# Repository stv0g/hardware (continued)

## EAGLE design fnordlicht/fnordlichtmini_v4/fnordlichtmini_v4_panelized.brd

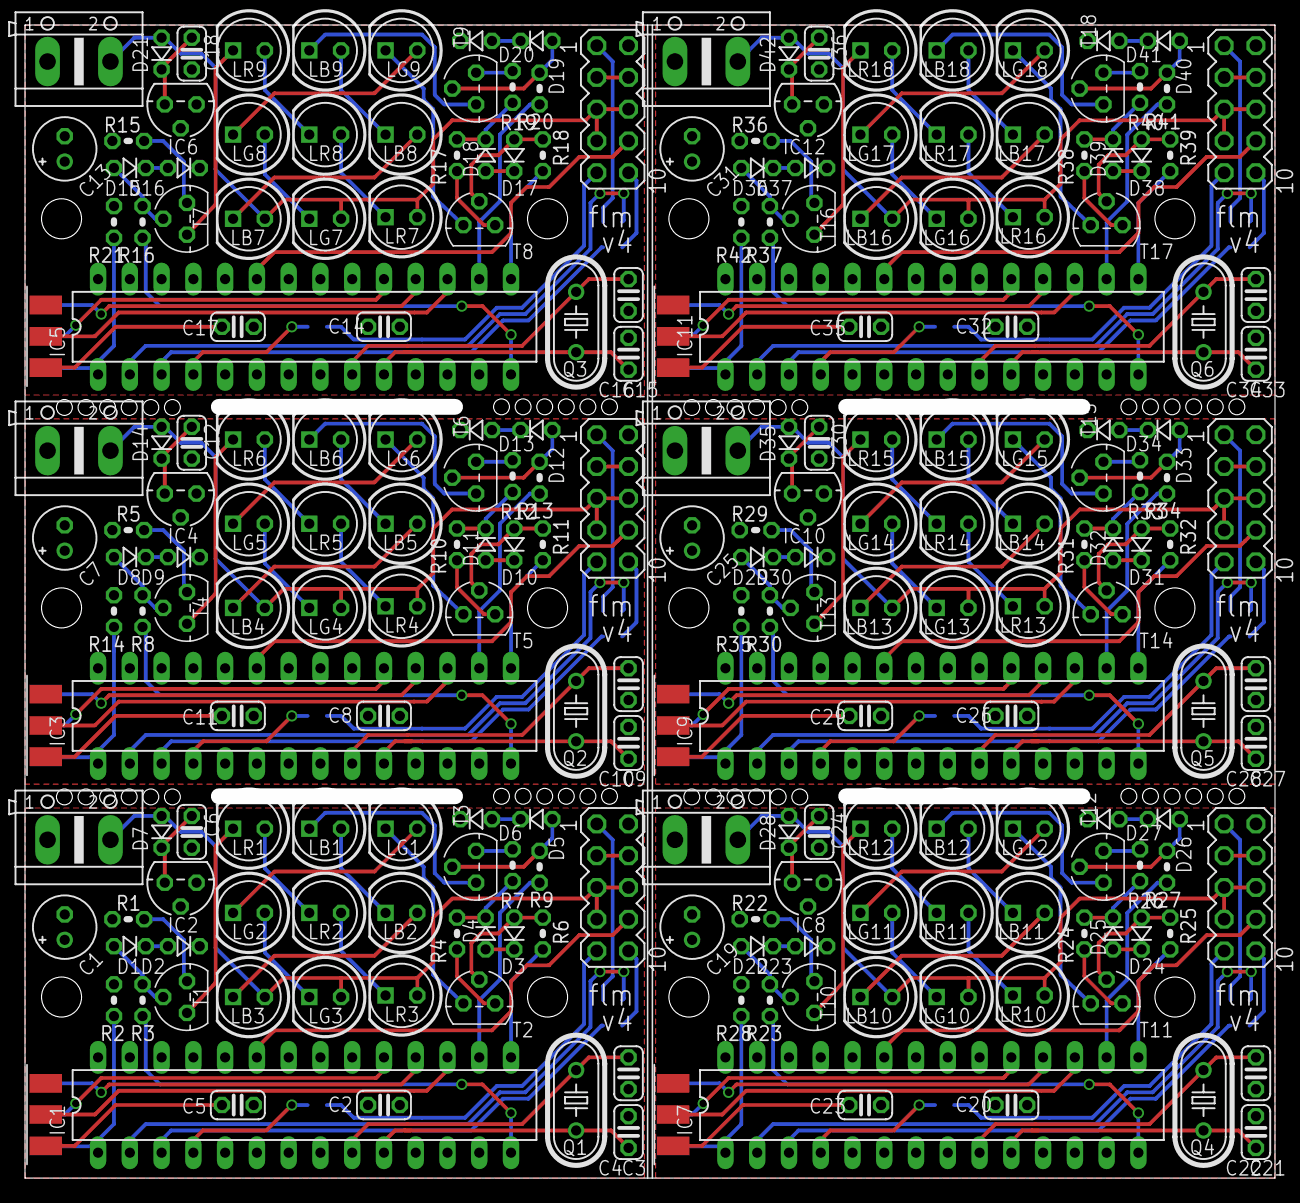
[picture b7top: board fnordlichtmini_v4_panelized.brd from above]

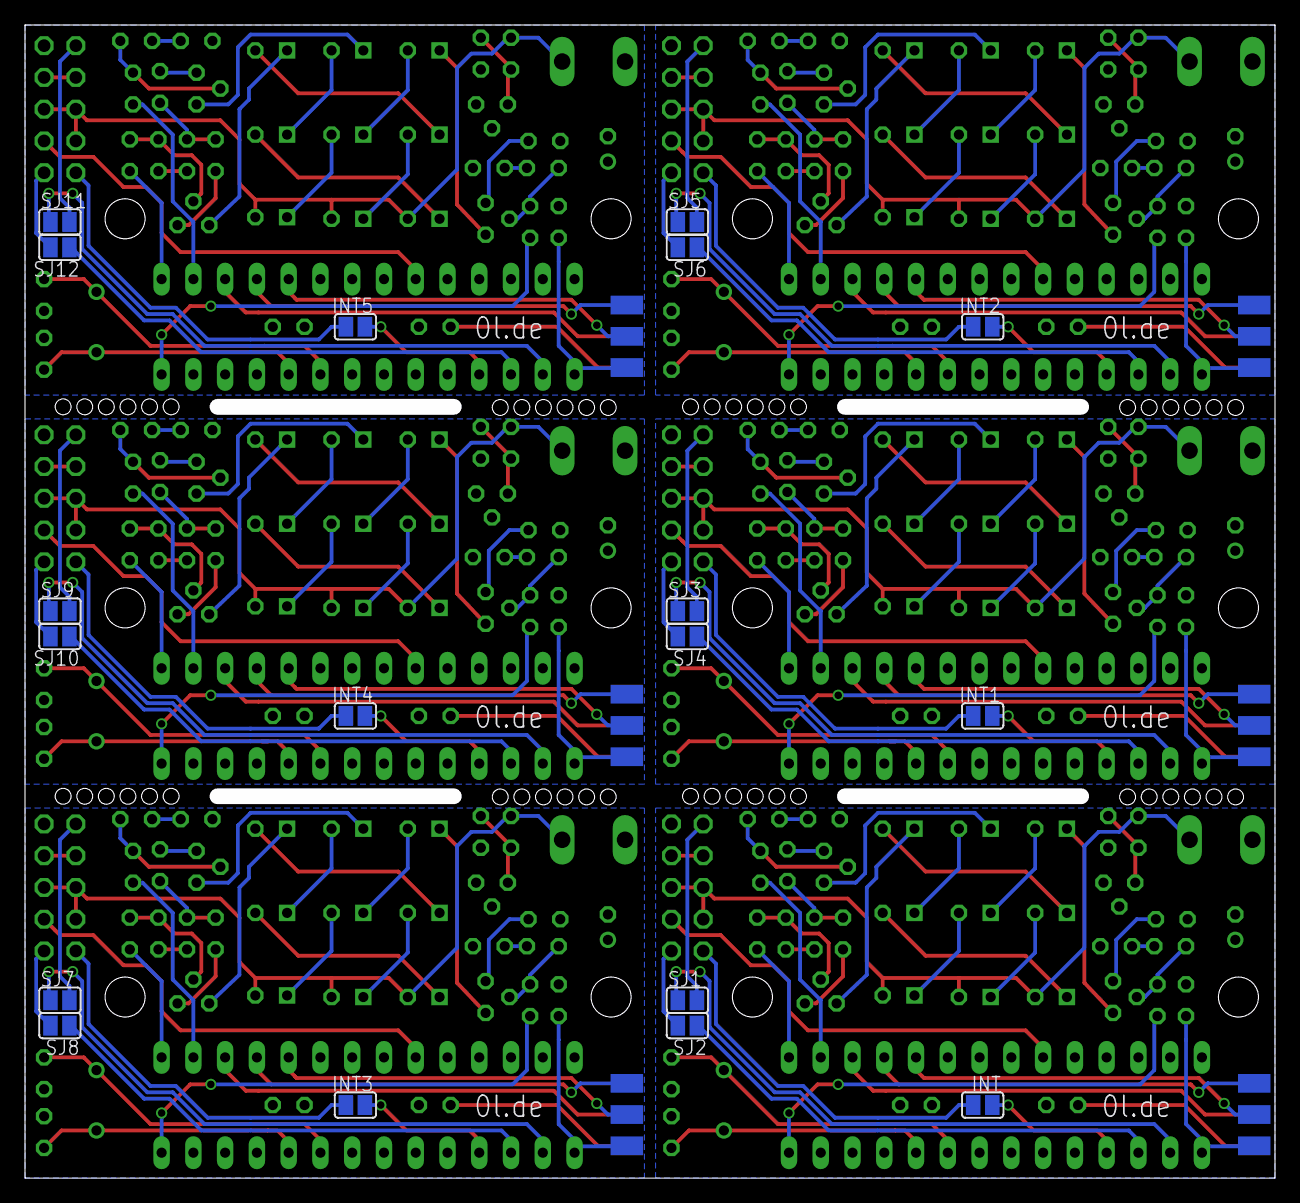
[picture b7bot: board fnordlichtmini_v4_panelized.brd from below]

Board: 2 copper layers, 99.9 x 92.2 mm, 246 parts (18 on the bottom side), 228 nets.

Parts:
C1, C7, C13, C19, C25, C31: 47uF; E2-5
C2, C5, C6, C8, C11, C12, C14, C17, C18, C20, C23, C24, C26, C29, C30, C32, C35, C36: 100n; C025-024X044
C3, C4, C9, C10, C15, C16, C21, C22, C27, C28, C33, C34: 33p; C025-024X044
D1, D2, D3, D4, D5, D6, D7, D8, D9, D10, D11, D12, D13, D14, D15, D16, D17, D18, D19, D20, D21, D22, D23, D24, D25, D26, D27, D28, D29, D30, D31, D32, D33, D34, D35, D36, D37, D38, D39, D40, D41, D42: D-2.5
IC1, IC3, IC5, IC7, IC9, IC11: MEGA8-P; DIL28-3
IC2, IC4, IC6, IC8, IC10, IC12: 78L05Z; TO92
INT, INT1, INT2, INT3, INT4, INT5: SJ
LB1, LB2, LB3, LB4, LB5, LB6, LB7, LB8, LB9, LB10, LB11, LB12, LB13, LB14, LB15, LB16, LB17, LB18: LED5MM
LG1, LG2, LG3, LG4, LG5, LG6, LG7, LG8, LG9, LG10, LG11, LG12, LG13, LG14, LG15, LG16, LG17, LG18: LED5MM
LR1, LR2, LR3, LR4, LR5, LR6, LR7, LR8, LR9, LR10, LR11, LR12, LR13, LR14, LR15, LR16, LR17, LR18: LED5MM
Q1, Q2, Q3, Q4, Q5, Q6: 16MHz; HC49U-V
R1, R4, R5, R7, R10, R12, R15, R17, R19, R22, R24, R26, R29, R31, R33, R36, R38, R40: 33R; 0204V
R2, R3, R6, R8, R9, R11, R13, R14, R16, R18, R20, R21, R23, R25, R27, R28, R30, R32, R34, R35, R37, R39, R41, R42: 2k2; 0204V
SJ1, SJ2, SJ3, SJ4, SJ5, SJ6, SJ7, SJ8, SJ9, SJ10, SJ11, SJ12: SJ
SV1, SV2, SV3, SV4, SV5, SV6: MA05-2
T1, T2, T3, T4, T5, T6, T7, T8, T9, T10, T11, T12, T13, T14, T15, T16, T17, T18: bc550c; TO92
U$1, U$2, U$3, U$4, U$5, U$6: AVR-ISP-6-EDGE; 6PAD_ISP
X1, X2, X3, X4, X5, X6: AK500/2

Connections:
+5V: C1.+, C2.1, C5.1, IC1.7, IC1.20, IC2.1, R2.1, U$1.VCC
+5V1: C7.+, C8.1, C11.1, IC3.7, IC3.20, IC4.1, R14.1, U$2.VCC
+5V2: C13.+, C14.1, C17.1, IC5.7, IC5.20, IC6.1, R21.1, U$3.VCC
+5V3: C19.+, C20.1, C23.1, IC7.7, IC7.20, IC8.1, R28.1, U$4.VCC
+5V4: C25.+, C26.1, C29.1, IC9.7, IC9.20, IC10.1, R35.1, U$5.VCC
+5V5: C31.+, C32.1, C35.1, IC11.7, IC11.20, IC12.1, R42.1, U$6.VCC
+12V: D7.A, LB3.A, LG3.A, LR3.A, SV1.5, SV1.6, SV1.7, X1.2
+12V1: D14.A, LB4.A, LG4.A, LR4.A, SV2.5, SV2.6, SV2.7, X2.2
+12V2: D21.A, LB7.A, LG7.A, LR7.A, SV3.5, SV3.6, SV3.7, X3.2
+12V3: D28.A, LB10.A, LG10.A, LR10.A, SV4.5, SV4.6, SV4.7, X4.2
+12V4: D35.A, LB13.A, LG13.A, LR13.A, SV5.5, SV5.6, SV5.7, X5.2
+12V5: D42.A, LB16.A, LG16.A, LR16.A, SV6.5, SV6.6, SV6.7, X6.2
ADC0: IC1.23, SV1.8
ADC1: IC3.23, SV2.8
ADC2: IC5.23, SV3.8
ADC3: IC7.23, SV4.8
ADC4: IC9.23, SV5.8
ADC5: IC11.23, SV6.8
BLUE: IC1.16, R9.2
BLUE1: IC3.16, R13.2
BLUE4: IC5.16, R20.2
BLUE6: IC7.16, R27.2
BLUE8: IC9.16, R34.2
BLUE10: IC11.16, R41.2
BUSINT: INT.2, SV1.9
BUSINT1: INT1.2, SV2.9
BUSINT2: INT2.2, SV3.9
BUSINT3: INT3.2, SV4.9
BUSINT4: INT4.2, SV5.9
BUSINT5: INT5.2, SV6.9
DATA1: SJ2.2, SV1.10
DATA2: SJ1.2, SV1.1
DATA3: SJ4.2, SV2.10
DATA4: SJ3.2, SV2.1
DATA5: SJ6.2, SV3.10
DATA6: SJ5.2, SV3.1
DATA7: SJ8.2, SV4.10
DATA8: SJ7.2, SV4.1
DATA9: SJ10.2, SV5.10
DATA10: SJ9.2, SV5.1
DATA11: SJ12.2, SV6.10
DATA12: SJ11.2, SV6.1
GND: C1.-, C2.2, C3.2, C4.2, C5.2, C6.2, D2.C, D4.C, D6.C, IC1.8, IC1.22, IC2.2, R1.2, R4.1, R7.1, SV1.2, SV1.3, SV1.4, U$1.GND, X1.1
GND1: C7.-, C8.2, C9.2, C10.2, C11.2, C12.2, D9.C, D11.C, D13.C, IC3.8, IC3.22, IC4.2, R5.2, R10.1, R12.1, SV2.2, SV2.3, SV2.4, U$2.GND, X2.1
GND2: C13.-, C14.2, C15.2, C16.2, C17.2, C18.2, D16.C, D18.C, D20.C, IC5.8, IC5.22, IC6.2, R15.2, R17.1, R19.1, SV3.2, SV3.3, SV3.4, U$3.GND, X3.1
GND3: C19.-, C20.2, C21.2, C22.2, C23.2, C24.2, D23.C, D25.C, D27.C, IC7.8, IC7.22, IC8.2, R22.2, R24.1, R26.1, SV4.2, SV4.3, SV4.4, U$4.GND, X4.1
GND4: C25.-, C26.2, C27.2, C28.2, C29.2, C30.2, D30.C, D32.C, D34.C, IC9.8, IC9.22, IC10.2, R29.2, R31.1, R33.1, SV5.2, SV5.3, SV5.4, U$5.GND, X5.1
GND5: C31.-, C32.2, C33.2, C34.2, C35.2, C36.2, D37.C, D39.C, D41.C, IC11.8, IC11.22, IC12.2, R36.2, R38.1, R40.1, SV6.2, SV6.3, SV6.4, U$6.GND, X6.1
GREEN: IC1.15, R6.1
GREEN1: IC3.15, R11.1
GREEN4: IC5.15, R18.1
GREEN6: IC7.15, R25.1
GREEN8: IC9.15, R32.1
GREEN10: IC11.15, R39.1
INT0: IC1.4, INT.1
INT1: IC3.4, INT1.1
INT2: IC5.4, INT2.1
INT3: IC7.4, INT3.1
INT4: IC9.4, INT4.1
INT5: IC11.4, INT5.1
MISO: IC1.18, U$1.MISO
MISO1: IC3.18, U$2.MISO
MISO2: IC5.18, U$3.MISO
MISO3: IC7.18, U$4.MISO
MISO4: IC9.18, U$5.MISO
MISO5: IC11.18, U$6.MISO
MOSI: IC1.17, U$1.MOSI
MOSI1: IC3.17, U$2.MOSI
MOSI2: IC5.17, U$3.MOSI
MOSI3: IC7.17, U$4.MOSI
MOSI4: IC9.17, U$5.MOSI
MOSI5: IC11.17, U$6.MOSI
unnamed: LR2.A, LR3.K
unnamed: LR1.A, LR2.K
unnamed: LR1.K, T1.3
unnamed: D1.C, D2.A
unnamed: R1.1, T1.1
unnamed: LR4.K, LR5.A
unnamed: D1.A, R3.2, T1.2
unnamed: LG2.A, LG3.K
unnamed: LG1.A, LG2.K
unnamed: LG1.K, T2.3
unnamed: D3.C, D4.A
unnamed: R4.2, T2.1
unnamed: LR5.K, LR6.A
unnamed: D3.A, R6.2, T2.2
unnamed: LB2.A, LB3.K
unnamed: LB1.A, LB2.K
unnamed: LB1.K, T3.3
unnamed: D5.C, D6.A
unnamed: R7.2, T3.1
unnamed: D8.C, D9.A
unnamed: D5.A, R9.1, T3.2
unnamed: C6.1, D7.C, IC2.3
unnamed: D8.A, R8.2, T4.2
unnamed: LG4.K, LG5.A
unnamed: LG5.K, LG6.A
unnamed: D10.C, D11.A
unnamed: D10.A, R11.2, T5.2
unnamed: LB4.K, LB5.A
unnamed: LB5.K, LB6.A
unnamed: D12.C, D13.A
unnamed: D12.A, R13.1, T6.2
unnamed: LR6.K, T4.3
unnamed: R5.1, T4.1
unnamed: LG6.K, T5.3
unnamed: R10.2, T5.1
unnamed: LB6.K, T6.3
unnamed: R12.2, T6.1
unnamed: C12.1, D14.C, IC4.3
unnamed: LR7.K, LR8.A
unnamed: LR8.K, LR9.A
unnamed: D15.C, D16.A
unnamed: D15.A, R16.2, T7.2
unnamed: LG7.K, LG8.A
unnamed: LG8.K, LG9.A
unnamed: D17.C, D18.A
unnamed: D17.A, R18.2, T8.2
unnamed: LB7.K, LB8.A
unnamed: LB8.K, LB9.A
unnamed: D19.C, D20.A
unnamed: D19.A, R20.1, T9.2
unnamed: LR9.K, T7.3
unnamed: R15.1, T7.1
unnamed: LG9.K, T8.3
unnamed: R17.2, T8.1
unnamed: LB9.K, T9.3
unnamed: R19.2, T9.1
unnamed: C18.1, D21.C, IC6.3
unnamed: LR10.K, LR11.A
unnamed: LR11.K, LR12.A
unnamed: D22.C, D23.A
unnamed: D22.A, R23.2, T10.2
unnamed: LG10.K, LG11.A
unnamed: LG11.K, LG12.A
unnamed: D24.C, D25.A
unnamed: D24.A, R25.2, T11.2
unnamed: LB10.K, LB11.A
unnamed: LB11.K, LB12.A
unnamed: D26.C, D27.A
unnamed: D26.A, R27.1, T12.2
unnamed: LR12.K, T10.3
unnamed: R22.1, T10.1
unnamed: LG12.K, T11.3
unnamed: R24.2, T11.1
unnamed: LB12.K, T12.3
unnamed: R26.2, T12.1
unnamed: C24.1, D28.C, IC8.3
unnamed: LR13.K, LR14.A
unnamed: LR14.K, LR15.A
unnamed: D29.C, D30.A
unnamed: D29.A, R30.2, T13.2
unnamed: LG13.K, LG14.A
unnamed: LG14.K, LG15.A
unnamed: D31.C, D32.A
unnamed: D31.A, R32.2, T14.2
unnamed: LB13.K, LB14.A
unnamed: LB14.K, LB15.A
unnamed: D33.C, D34.A
unnamed: D33.A, R34.1, T15.2
unnamed: LR15.K, T13.3
unnamed: R29.1, T13.1
unnamed: LG15.K, T14.3
unnamed: R31.2, T14.1
unnamed: LB15.K, T15.3
unnamed: R33.2, T15.1
unnamed: C30.1, D35.C, IC10.3
unnamed: LR16.K, LR17.A
unnamed: LR17.K, LR18.A
unnamed: D36.C, D37.A
unnamed: D36.A, R37.2, T16.2
unnamed: LG16.K, LG17.A
unnamed: LG17.K, LG18.A
unnamed: D38.C, D39.A
unnamed: D38.A, R39.2, T17.2
unnamed: LB16.K, LB17.A
unnamed: LB17.K, LB18.A
unnamed: D40.C, D41.A
unnamed: D40.A, R41.1, T18.2
unnamed: LR18.K, T16.3
unnamed: R36.1, T16.1
unnamed: LG18.K, T17.3
unnamed: R38.2, T17.1
unnamed: LB18.K, T18.3
unnamed: R40.2, T18.1
unnamed: C36.1, D42.C, IC12.3
RED: IC1.14, R3.1
RED1: IC3.14, R8.1
RED4: IC5.14, R16.1
RED6: IC7.14, R23.1
RED8: IC9.14, R30.1
RED10: IC11.14, R37.1
RST: IC1.1, R2.2, U$1.RST
RST1: IC3.1, R14.2, U$2.RST
RST2: IC5.1, R21.2, U$3.RST
RST3: IC7.1, R28.2, U$4.RST
RST4: IC9.1, R35.2, U$5.RST
RST5: IC11.1, R42.2, U$6.RST
RX: IC1.2, SJ1.1
RX1: IC3.2, SJ3.1
RX2: IC5.2, SJ5.1
RX3: IC7.2, SJ7.1
RX4: IC9.2, SJ9.1
RX5: IC11.2, SJ11.1
SCK: IC1.19, U$1.SCK
SCK1: IC3.19, U$2.SCK
SCK2: IC5.19, U$3.SCK
SCK3: IC7.19, U$4.SCK
SCK4: IC9.19, U$5.SCK
SCK5: IC11.19, U$6.SCK
TX: IC1.3, SJ2.1
TX1: IC3.3, SJ4.1
TX2: IC5.3, SJ6.1
TX3: IC7.3, SJ8.1
TX4: IC9.3, SJ10.1
TX5: IC11.3, SJ12.1
XTAL1: C3.1, IC1.9, Q1.1
XTAL2: C4.1, IC1.10, Q1.2
XTAL3: C9.1, IC3.9, Q2.1
XTAL4: C10.1, IC3.10, Q2.2
XTAL5: C15.1, IC5.9, Q3.1
XTAL6: C16.1, IC5.10, Q3.2
XTAL7: C21.1, IC7.9, Q4.1
XTAL8: C22.1, IC7.10, Q4.2
XTAL9: C27.1, IC9.9, Q5.1
XTAL10: C28.1, IC9.10, Q5.2
XTAL11: C33.1, IC11.9, Q6.1
XTAL12: C34.1, IC11.10, Q6.2

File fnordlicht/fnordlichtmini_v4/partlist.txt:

Partlist

Exported from fnordlichtmini_v4.sch at 05.01.14 00:12

EAGLE Version 6.1.0 Copyright (c) 1988-2012 CadSoft

Assembly variant: 

Part     Value          Device          Package      Library    Sheet

C1       47uF           CPOL-EUE2-5     E2-5         rcl        1
C2       100n           C-EU025-024X044 C025-024X044 rcl        1
C3       33p            C-EU025-024X044 C025-024X044 rcl        1
C4       33p            C-EU025-024X044 C025-024X044 rcl        1
C5       100n           C-EU025-024X044 C025-024X044 rcl        1
C6       100n           C-EU025-024X044 C025-024X044 rcl        1
D1                      DIODE-D-2.5     D-2.5        diode      1
D2                      DIODE-D-2.5     D-2.5        diode      1
D3                      DIODE-D-2.5     D-2.5        diode      1
D4                      DIODE-D-2.5     D-2.5        diode      1
D5                      DIODE-D-2.5     D-2.5        diode      1
D6                      DIODE-D-2.5     D-2.5        diode      1
D7                      DIODE-D-2.5     D-2.5        diode      1
IC1      MEGA8-P        MEGA8-P         DIL28-3      atmel      1
IC2      78L05Z         78L05Z          TO92         linear     1
INT                     SJ              SJ           jumper     1
LB1                     LED5MM          LED5MM       led-mark   1
LB2                     LED5MM          LED5MM       led-mark   1
LB3                     LED5MM          LED5MM       led-mark   1
LG1                     LED5MM          LED5MM       led-mark   1
LG2                     LED5MM          LED5MM       led-mark   1
LG3                     LED5MM          LED5MM       led-mark   1
LR1                     LED5MM          LED5MM       led-mark   1
LR2                     LED5MM          LED5MM       led-mark   1
LR3                     LED5MM          LED5MM       led-mark   1
Q1       16MHz          CRYSTALHC49U-V  HC49U-V      crystal    1
R1       33R            R-EU_0204/2V    0204V        rcl        1
R2       2k2            R-EU_0204/2V    0204V        rcl        1
R3       2k2            R-EU_0204/2V    0204V        rcl        1
R4       33R            R-EU_0204/2V    0204V        rcl        1
R6       2k2            R-EU_0204/2V    0204V        rcl        1
R7       33R            R-EU_0204/2V    0204V        rcl        1
R9       2k2            R-EU_0204/2V    0204V        rcl        1
SJ1                     SJ              SJ           jumper     1
SJ2                     SJ              SJ           jumper     1
SV1                     MA05-2          MA05-2       con-lstb   1
T1       bc550c         -NPN-TO92       TO92         transistor 1
T2       bc550c         -NPN-TO92       TO92         transistor 1
T3       bc550c         -NPN-TO92       TO92         transistor 1
U$1      AVR-ISP-6-EDGE AVR-ISP-6-EDGE  6PAD_ISP     isp        1
X1                      AK500/2         AK500/2      con-ptr500 1
